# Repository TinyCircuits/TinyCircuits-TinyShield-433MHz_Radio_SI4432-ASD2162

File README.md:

# TinyCircuits TinyShield 433MHz radio (SI4432)
# ASD2162 Rev3

The design files are located under design-files/ for the TinyCircuits ASD2162 Rev3 PCB.  This is a TinyShield board that has a SI4432 433MHz radio transceiver and can communicate over a long distance.   

Format is in Cadsoft Eagle format - Eagle version 6.2 was used for the original design.

For more infomation on this, check out the product page at TinyCircuits.com:  https://tinycircuits.com/collections/communication/products/433mhz-long-range-radio-tinyshield

# License:

Design by TinyCircuits.
All design files are released under the Creative Commons Attribution Share-Alike 3.0 License, see the following link for details: http://creativecommons.org/licenses/by-sa/3.0

All text above must be included in any redistribution or derived design

This project uses designs and concepts developed as part of the Arduino project and the LilyPad project.  The TinyCircuits design files themselves (schematics, PCB and libraries) are not directly derived from these works' design files and have been created new, however the concepts and basic architecture behind the TinyDuino and TinyLily products are derived and we thank the hard work of the organizations below for their contributions to open-source hardware:
  
Original Arduino Uno Design by Team Arduino

LilyPad Arduino Design by Leah Buechley and Sparkfun Electronics

Please support the open-source hardware community

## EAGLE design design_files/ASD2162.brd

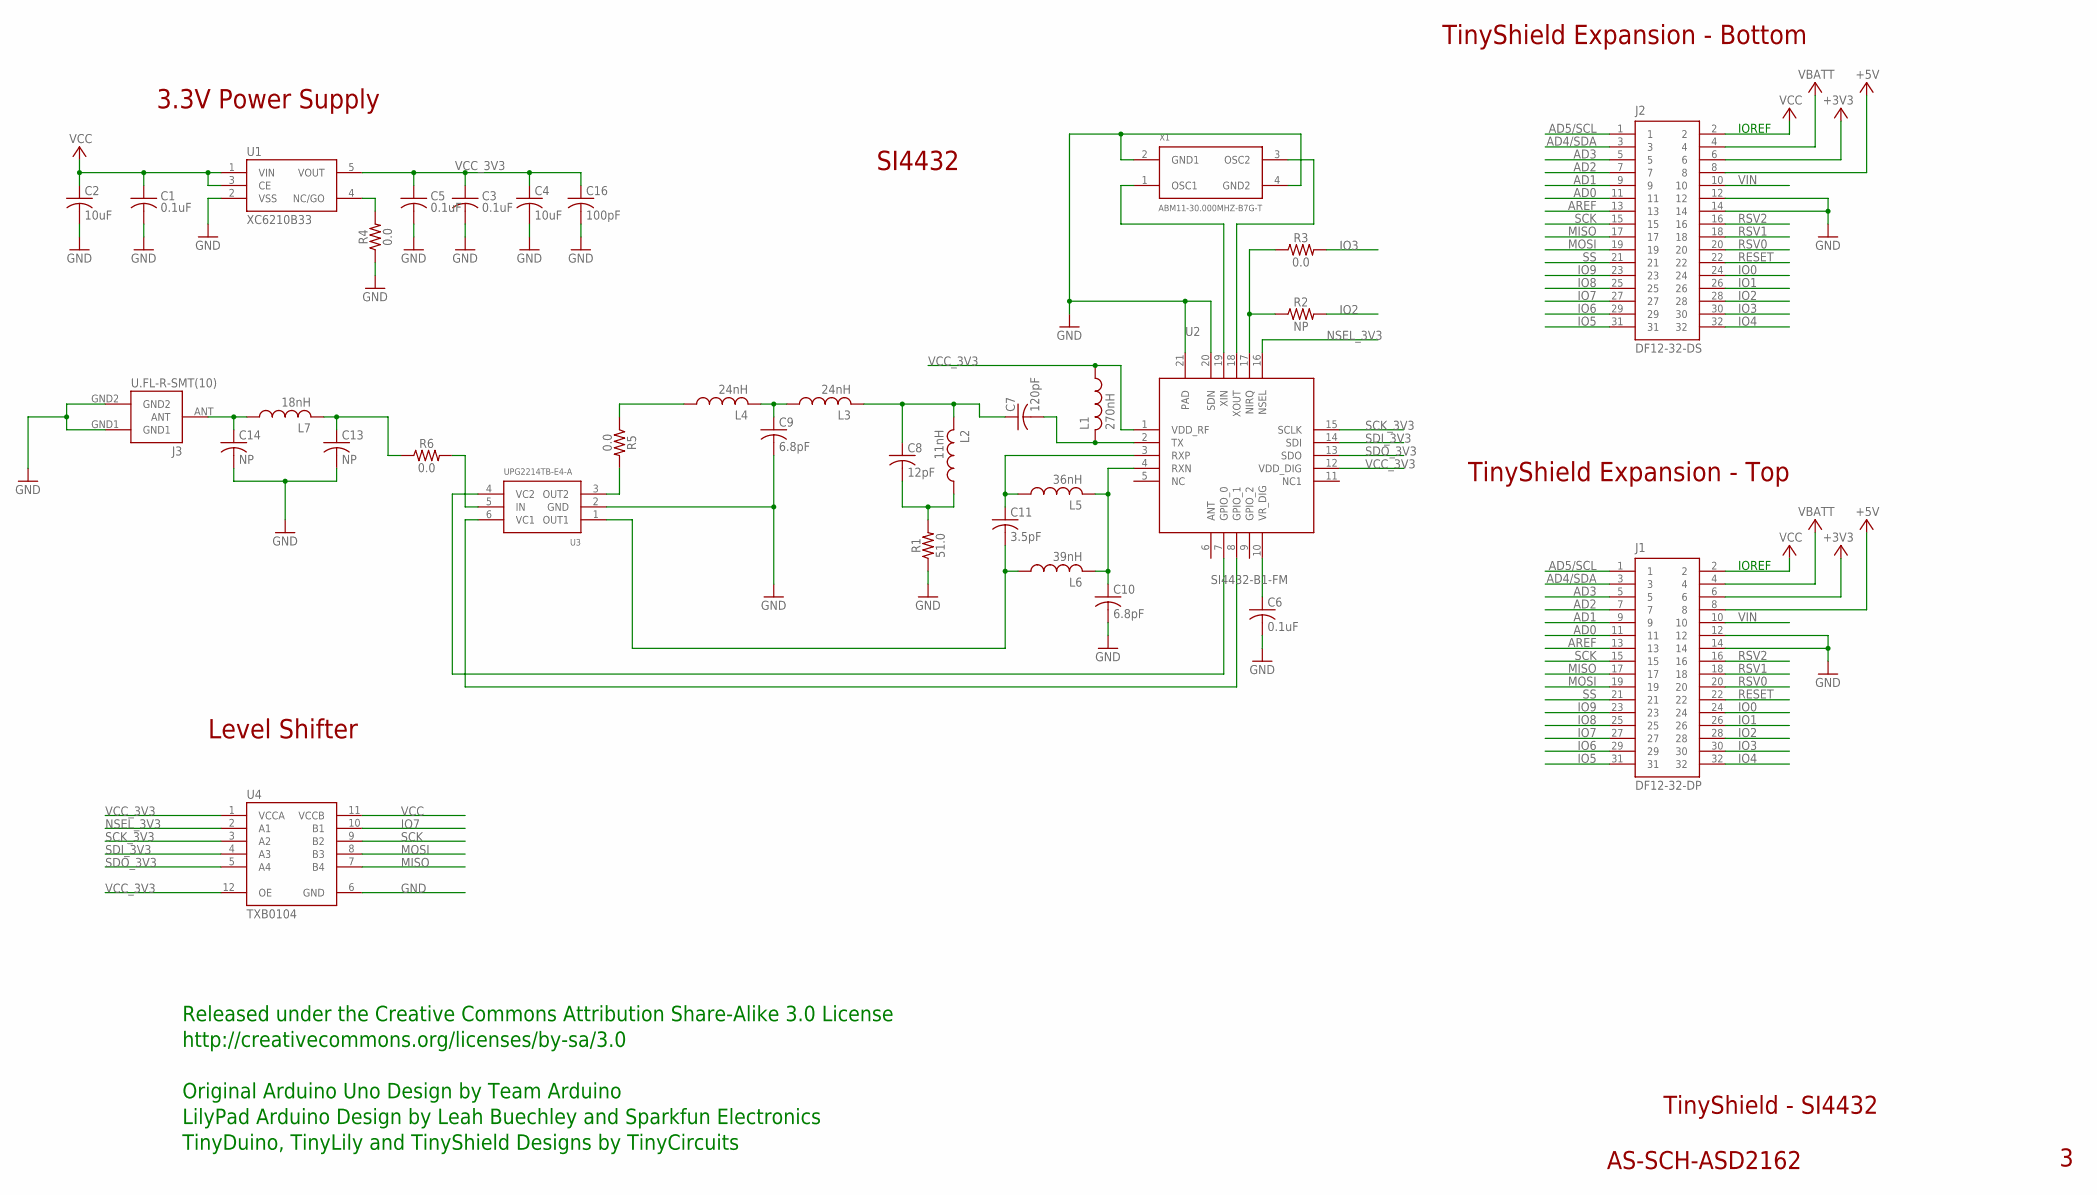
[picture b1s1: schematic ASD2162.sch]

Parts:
C1, C3, C5, C6: 0.1uF; C0402; PARTNO AS-ITM-00008
C2, C4: 10uF; C0805; PARTNO AS-ITM-00045
C7: 120pF; C0402
C8: 12pF; C0402; PARTNO AS-ITM-00261
C9, C10: 6.8pF; C0402; PARTNO AS-ITM-00252
C11: 3.5pF; C0402; PARTNO AS-ITM-00258
C13, C14: NP; C0402; PARTNO AS-ITM-00084
C16: 100pF; 0402
J1: DF12-32-DP; PARTNO AS-ITM-00015
J2: DF12-32-DS; PARTNO AS-ITM-00012
J3: U.FL-R-SMT(10)
L1: 270nH; C0402; PARTNO AS-ITM-00250
L2: 11nH; C0402; PARTNO AS-ITM-00254
L3, L4: 24nH; C0402; PARTNO AS-ITM-00257
L5: 36nH; C0402; PARTNO AS-ITM-00253
L6: 39nH; C0402; PARTNO AS-ITM-00259
L7: 18nH; C0402; PARTNO AS-ITM-00260
R1: 51.0; 0402; PARTNO AS-ITM-00262
R2: NP; 0402
R3, R4: 0.0; 0402
R5, R6: 0.0; C0402; PARTNO AS-ITM-00076
U1: XC6210B33; SOT-25
U2: SI4432-B1-FM; QFN20
U3: UPG2214TB-E4-A; S06
U4: TXB0104; UQFN-12
X1: ABM11-30.000MHZ-B7G-T; ABM11

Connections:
+3V3: J1.6, J2.6
+5V: J1.8, J2.8
AD0: J1.11, J2.11
AD1: J1.9, J2.9
AD2: J1.7, J2.7
AD3: J1.5, J2.5
AD4/SDA: J1.3, J2.3
AD5/SCL: J1.1, J2.1
AREF: J1.13, J2.13
GND: C1.2, C2.2, C3.2, C4.2, C5.2, C6.2, C9.2, C10.2, C13.2, C14.2, C16.2, J1.12, J1.14, J2.12, J2.14, J3.GND1, J3.GND2, R1.1, R4.1, U1.2 (VSS), U2.20 (SDN), U2.21 (PAD), U3.2 (GND), U4.6 (GND), X1.2 (GND1), X1.4 (GND2)
IO0: J1.24, J2.24
IO1: J1.26, J2.26
IO2: J1.28, J2.28, R2.2
IO3: J1.30, J2.30, R3.2
IO4: J1.32, J2.32
IO5: J1.31, J2.31
IO6: J1.29, J2.29
IO7: J1.27, J2.27, U4.10 (B1)
IO8: J1.25, J2.25
IO9: J1.23, J2.23
MISO: J1.17, J2.17, U4.7 (B4)
MOSI: J1.19, J2.19, U4.8 (B3)
unnamed: U2.19 (XIN), X1.1 (OSC1)
unnamed: U2.18 (XOUT), X1.3 (OSC2)
unnamed: C10.1, L5.2, L6.2, U2.4 (RXN)
unnamed: C7.2, L1.2, U2.2 (TX)
unnamed: C6.1, U2.10 (VR_DIG)
unnamed: C7.1, C8.1, L2.2, L3.2
unnamed: C8.2, L2.1, R1.2
unnamed: C9.1, L3.1, L4.2
unnamed: C11.1, L5.1, U2.3 (RXP)
unnamed: R5.2, U3.3 (OUT2)
unnamed: C11.2, L6.1, U3.1 (OUT1)
unnamed: U2.7 (GPIO_0), U3.4 (VC2)
unnamed: U2.8 (GPIO_1), U3.6 (VC1)
unnamed: L4.1, R5.1
unnamed: R6.2, U3.5 (IN)
unnamed: C13.1, L7.2, R6.1
unnamed: C14.1, J3.ANT, L7.1
unnamed: R2.1, R3.1, U2.17 (NIRQ)
unnamed: R4.2, U1.4 (NC/GO)
NSEL_3V3: U2.16 (NSEL), U4.2 (A1)
RESET: J1.22, J2.22
RSV0: J1.20, J2.20
RSV1: J1.18, J2.18
RSV2: J1.16, J2.16
SCK: J1.15, J2.15, U4.9 (B2)
SCK_3V3: U2.15 (SCLK), U4.3 (A2)
SDI_3V3: U2.14 (SDI), U4.4 (A3)
SDO_3V3: U2.13 (SDO), U4.5 (A4)
SS: J1.21, J2.21
VBATT: J1.4, J2.4
VCC: C1.1, C2.1, J1.2, J2.2, U1.1 (VIN), U1.3 (CE), U4.11 (VCCB)
VCC_3V3: C3.1, C4.1, C5.1, C16.1, L1.1, U1.5 (VOUT), U2.1 (VDD_RF), U2.12 (VDD_DIG), U4.1 (VCCA), U4.12 (OE)
VIN: J1.10, J2.10

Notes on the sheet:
TinyShield Expansion - Bottom
TinyShield - SI4432
AS-SCH-ASD2162
TinyShield Expansion - Top
IOREF
Released under the Creative Commons Attribution Share-Alike 3.0 License
http://creativecommons.org/licenses/by-sa/3.0
LilyPad Arduino Design by Leah Buechley and Sparkfun Electronics
TinyDuino, TinyLily and TinyShield Designs by TinyCircuits
Original Arduino Uno Design by Team Arduino
3.3V Power Supply
Level Shifter
SI4432

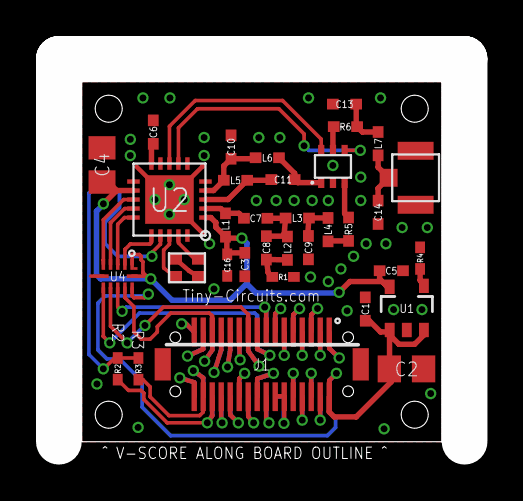
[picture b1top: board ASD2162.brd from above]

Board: 2 copper layers, 20.0 x 20.0 mm, 36 parts (1 on the bottom side), 55 nets.

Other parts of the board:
U$1: DOCFIELD-TINYCIRCUITS-PCB

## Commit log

2015-04-11 :octocat: Added .gitattributes & .gitignore files
2019-01-02 update format
2019-01-07 updated comments
2019-05-22 added images
2019-05-23 updated images
2019-05-28 added examples and libraries
2019-06-04 added tutorial images
2019-06-04 added tutorial sketches
2019-06-04 commented code
2020-02-11 image update
2020-07-28 Add CAD data
2020-08-14 Update CAD drawing
